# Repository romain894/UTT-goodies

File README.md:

# UTT-goodies
Keychain and LED decoration

## Licence :

This work is licensed under a <a rel="license" href="http://creativecommons.org/licenses/by-sa/4.0/">Creative Commons Attribution-ShareAlike 4.0 International License</a>.

Romain THOMAS 2020

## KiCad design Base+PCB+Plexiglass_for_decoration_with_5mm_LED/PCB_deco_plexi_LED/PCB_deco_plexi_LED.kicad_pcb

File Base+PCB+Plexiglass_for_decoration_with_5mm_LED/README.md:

# UTT LED decoration

The manufacturing of this project has been through CNC and PCB milling and 3D printing.

It was originally created for a high school workshop : each student designed its own and then made it.

## PCB :

You can find it in the PCB_deco_plexi_LED directory, it was made with KiCad.

## Base :

It was made with FreeCAD : Base_3D_printer_deco_led.FCStd

There is also an STL export : Base.stl

## Plexiglass :

It has been made especially for the UTT CNC software (charly robot) : LogoPlexiUTT.grl

## Licence :

This work is licensed under a <a rel="license" href="http://creativecommons.org/licenses/by-sa/4.0/">Creative Commons Attribution-ShareAlike 4.0 International License</a>.

Romain THOMAS 2020

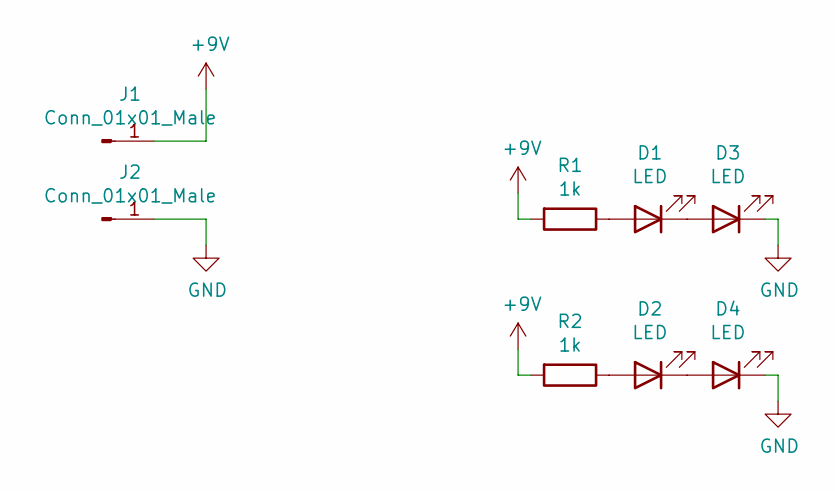
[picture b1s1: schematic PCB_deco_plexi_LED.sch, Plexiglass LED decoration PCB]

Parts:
D1, D2, D3, D4: LED; LED_D5.0mm_Clear
J1, J2: Conn_01x01_Male; PinSocket_1x01_P2.54mm_Vertical
R1, R2: 1k; R_Axial_DIN0207_L6.3mm_D2.5mm_P7.62mm_Horizontal

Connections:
+9V: J1.1, R1.2, R2.2
GND: D3.1 (K), D4.1 (K), J2.1
unnamed: D1.1 (K), D3.2 (A)
unnamed: D1.2 (A), R1.1
unnamed: D2.1 (K), D4.2 (A)
unnamed: D2.2 (A), R2.1

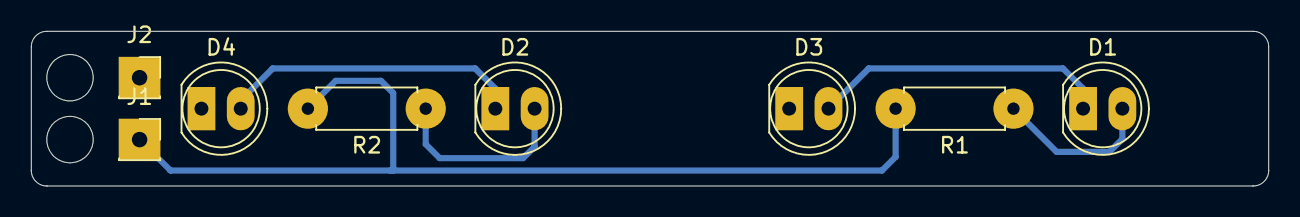
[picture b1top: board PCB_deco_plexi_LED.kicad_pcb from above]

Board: 2 copper layers, 80.0 x 10.0 mm, 8 parts (0 on the bottom side), 6 nets.

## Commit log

2021-03-28 first commit with files
